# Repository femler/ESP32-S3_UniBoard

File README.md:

# ESP32-S3_UniBoard
Universal Board for ESP32-S3

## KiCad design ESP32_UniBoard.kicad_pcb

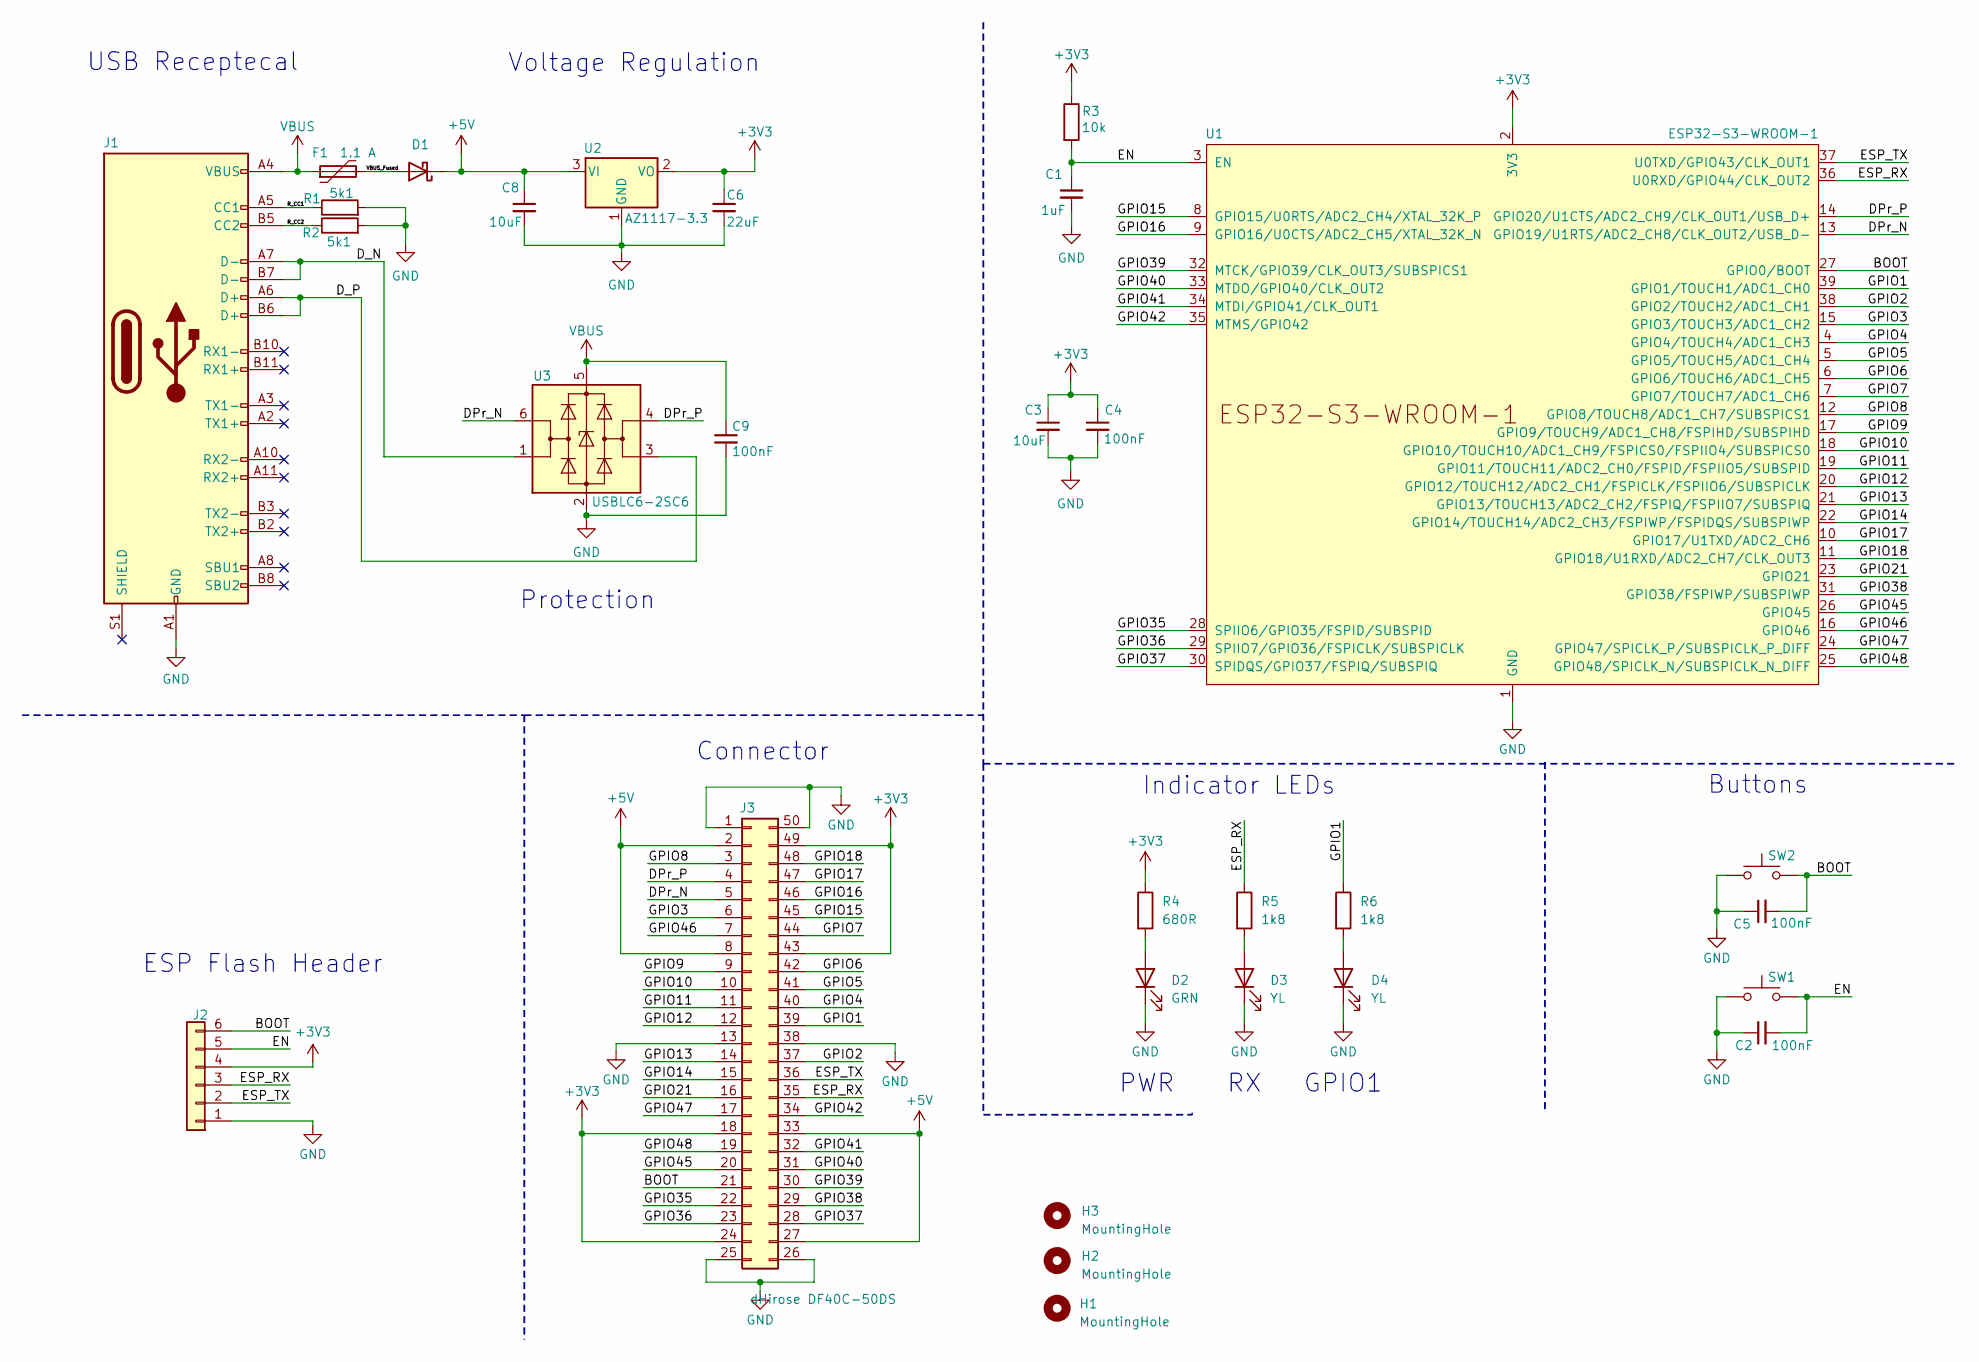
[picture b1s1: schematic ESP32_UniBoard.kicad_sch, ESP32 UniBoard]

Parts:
C1: 1uF; C_0603_1608Metric; JLCPCB Part # C15849
C2, C4, C5, C9: 100nF; C_0603_1608Metric; JLCPCB Part # C14663
C3, C8: 10uF; C_0603_1608Metric; JLCPCB Part # C19702
C6: 22uF; C_0805_2012Metric; JLCPCB Part # C59461
D1: B5819W SL; D_SOD-123; JLCPCB Part # C8598
D2: GRN; LED_0603_1608Metric; JLCPCB Part # C2833058
D3, D4: YL; LED_0603_1608Metric; JLCPCB Part # C131265
F1: 1.1 A; Fuse_0805_2012Metric; JLCPCB Part # C207024
H1, H2, H3: MountingHole; MountingHole_2.7mm_M2.5
J1: USB_C_Receptacle_USB2.0; USB_C_Receptacle_G-Switch_GT-USB-7010ASV; JLCPCB Part # C2988369
J2: Conn_01x06_Socket; PinHeader_1x06_P2.54mm_Vertical
J3: dHirose DF40C-50DS; Hirose_DF40C-50DS; JLCPCB Part # C424646
R1, R2: 5k1; R_0603_1608Metric; JLCPCB Part # C144594
R3: 10k; R_0603_1608Metric; JLCPCB Part # C116677
R4: 680R; R_0603_1608Metric; JLCPCB Part # C115415
R5, R6: 1k8; R_0603_1608Metric; JLCPCB Part # C228145
SW1, SW2: SW_Push; SW_Tactile_SPST_NO_Straight_CK_PTS636Sx25SMTRLFS; JLCPCB Part # C354943
U1: ESP32-S3-WROOM-1; JLCPCB Part # C2913198
U2: AZ1117-3.3; SOT-223-3_TabPin2; JLCPCB Part # C92102
U3: USBLC6-2SC6; SOT-23-6; JLCPCB Part # C5261088

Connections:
+3V3: C3.1, C4.1, C6.1, J2.4, J3.18, J3.24, J3.43, J3.49, R3.1, R4.1, U1.2 (3V3), U2.2 (VO)
+5V: C8.1, D1.1 (K), J3.2, J3.8, J3.27, J3.33, U2.3 (VI)
/BOOT: C5.2, J2.6, J3.21, SW2.2, U1.27 (GPIO0/BOOT)
/DPr_N: J3.5, U1.13 (GPIO19/U1RTS/ADC2_CH8/CLK_OUT2/USB_D-), U3.6 (I/O1)
/DPr_P: J3.4, U1.14 (GPIO20/U1CTS/ADC2_CH9/CLK_OUT1/USB_D+), U3.4 (I/O2)
/D_N: J1.A7 (D-), J1.B7 (D-), U3.1 (I/O1)
/D_P: J1.A6 (D+), J1.B6 (D+), U3.3 (I/O2)
/EN: C1.1, C2.2, J2.5, R3.2, SW1.2, U1.3 (EN)
/ESP_RX: J2.3, J3.35, R5.1, U1.36 (U0RXD/GPIO44/CLK_OUT2)
/ESP_TX: J2.2, J3.36, U1.37 (U0TXD/GPIO43/CLK_OUT1)
/GPIO1: J3.39, R6.1, U1.39 (GPIO1/TOUCH1/ADC1_CH0)
/GPIO2: J3.37, U1.38 (GPIO2/TOUCH2/ADC1_CH1)
/GPIO3: J3.6, U1.15 (GPIO3/TOUCH3/ADC1_CH2)
/GPIO4: J3.40, U1.4 (GPIO4/TOUCH4/ADC1_CH3)
/GPIO5: J3.41, U1.5 (GPIO5/TOUCH5/ADC1_CH4)
/GPIO6: J3.42, U1.6 (GPIO6/TOUCH6/ADC1_CH5)
/GPIO7: J3.44, U1.7 (GPIO7/TOUCH7/ADC1_CH6)
/GPIO8: J3.3, U1.12 (GPIO8/TOUCH8/ADC1_CH7/SUBSPICS1)
/GPIO9: J3.9, U1.17 (GPIO9/TOUCH9/ADC1_CH8/FSPIHD/SUBSPIHD)
/GPIO10: J3.10, U1.18 (GPIO10/TOUCH10/ADC1_CH9/FSPICS0/FSPIIO4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)
/GPIO11: J3.11, U1.19 (GPIO11/TOUCH11/ADC2_CH0/FSPID/FSPIIO5/S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)
/GPIO12: J3.12, U1.20 (GPIO12/TOUCH12/ADC2_CH1/FSPICLK/FSPIIO6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)
/GPIO13: J3.14, U1.21 (GPIO13/TOUCH13/ADC2_CH2/FSPIQ/FSPIIO7/S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)
/GPIO14: J3.15, U1.22 (GPIO14/TOUCH14/ADC2_CH3/FSPIWP/FSPIDQS/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)
/GPIO15: J3.45, U1.8 (GPIO15/U0RTS/ADC2_CH4/XTAL_32K_P)
/GPIO16: J3.46, U1.9 (GPIO16/U0CTS/ADC2_CH5/XTAL_32K_N)
/GPIO17: J3.47, U1.10 (GPIO17/U1TXD/ADC2_CH6)
/GPIO18: J3.48, U1.11 (GPIO18/U1RXD/ADC2_CH7/CLK_OUT3)
/GPIO21: J3.16, U1.23 (GPIO21)
/GPIO35: J3.22, U1.28 (SPIIO6/GPIO35/FSPID/SUBSPID)
/GPIO36: J3.23, U1.29 (SPIIO7/GPIO36/FSPICLK/SUBSPICLK)
/GPIO37: J3.28, U1.30 (SPIDQS/GPIO37/FSPIQ/SUBSPIQ)
/GPIO38: J3.29, U1.31 (GPIO38/FSPIWP/SUBSPIWP)
/GPIO39: J3.30, U1.32 (MTCK/GPIO39/CLK_OUT3/SUBSPICS1)
/GPIO40: J3.31, U1.33 (MTDO/GPIO40/CLK_OUT2)
/GPIO41: J3.32, U1.34 (MTDI/GPIO41/CLK_OUT1)
/GPIO42: J3.34, U1.35 (MTMS/GPIO42)
/GPIO45: J3.20, U1.26 (GPIO45)
/GPIO46: J3.7, U1.16 (GPIO46)
/GPIO47: J3.17, U1.24 (GPIO47/SPICLK_P/SUBSPICLK_P_DIFF)
/GPIO48: J3.19, U1.25 (GPIO48/SPICLK_N/SUBSPICLK_N_DIFF)
/R_CC1: J1.A5 (CC1), R1.1
/R_CC2: J1.B5 (CC2), R2.1
/VBUS_Fused: D1.2 (A), F1.2
GND: C1.2, C2.1, C3.2, C4.2, C5.1, C6.2, C8.2, C9.2, D2.1 (K), D3.1 (K), D4.1 (K), J1.A1 (GND), J1.A12 (GND), J1.B1 (GND), J1.B12 (GND), J2.1, J3.1, J3.13, J3.25, J3.26, J3.38, J3.50, R1.2, R2.2, SW1.1, SW2.1, U1.1 (GND), U1.40 (GND), U1.41 (GND), U2.1 (GND), U3.2 (GND)
unnamed: D2.2 (A), R4.2
unnamed: D3.2 (A), R5.2
unnamed: D4.2 (A), R6.2
VBUS: C9.1, F1.1, J1.A4 (VBUS), J1.A9 (VBUS), J1.B4 (VBUS), J1.B9 (VBUS), U3.5 (VBUS)

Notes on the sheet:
GPIO1
Protection
Voltage Regulation
ESP Flash Header
USB Receptecal
Indicator LEDs
PWR
Buttons
Connector

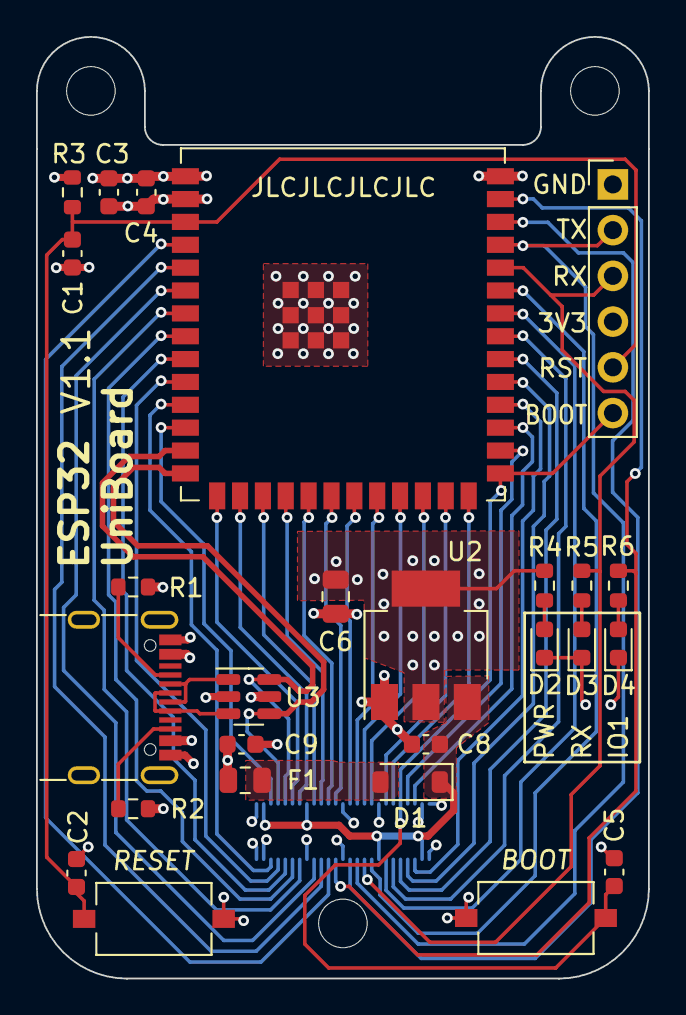
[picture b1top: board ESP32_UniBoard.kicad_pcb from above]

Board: 4 copper layers, 34.0 x 52.3 mm, 30 parts (1 on the bottom side), 49 nets.

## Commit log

2023-06-02 Added .gitignore
2023-06-02 Create LICENSE
2023-06-04 Schematics and PCB updates
2023-06-06 Start of PCB routing
2023-06-07 PCB rework
2023-06-10 Routing complete
2023-06-11 Screenshots generated
2023-06-14 Adjustments in Schematic and PCB
2023-06-23 PCB changed to 4 Layer WIP
2023-06-25 Additional routing~
2023-06-25 Routing 4 Layer Board complete
2023-06-26 Slight changes and added JLCPCB part numbers
2023-06-26 Gerber files generated
2023-06-30 Test for production
